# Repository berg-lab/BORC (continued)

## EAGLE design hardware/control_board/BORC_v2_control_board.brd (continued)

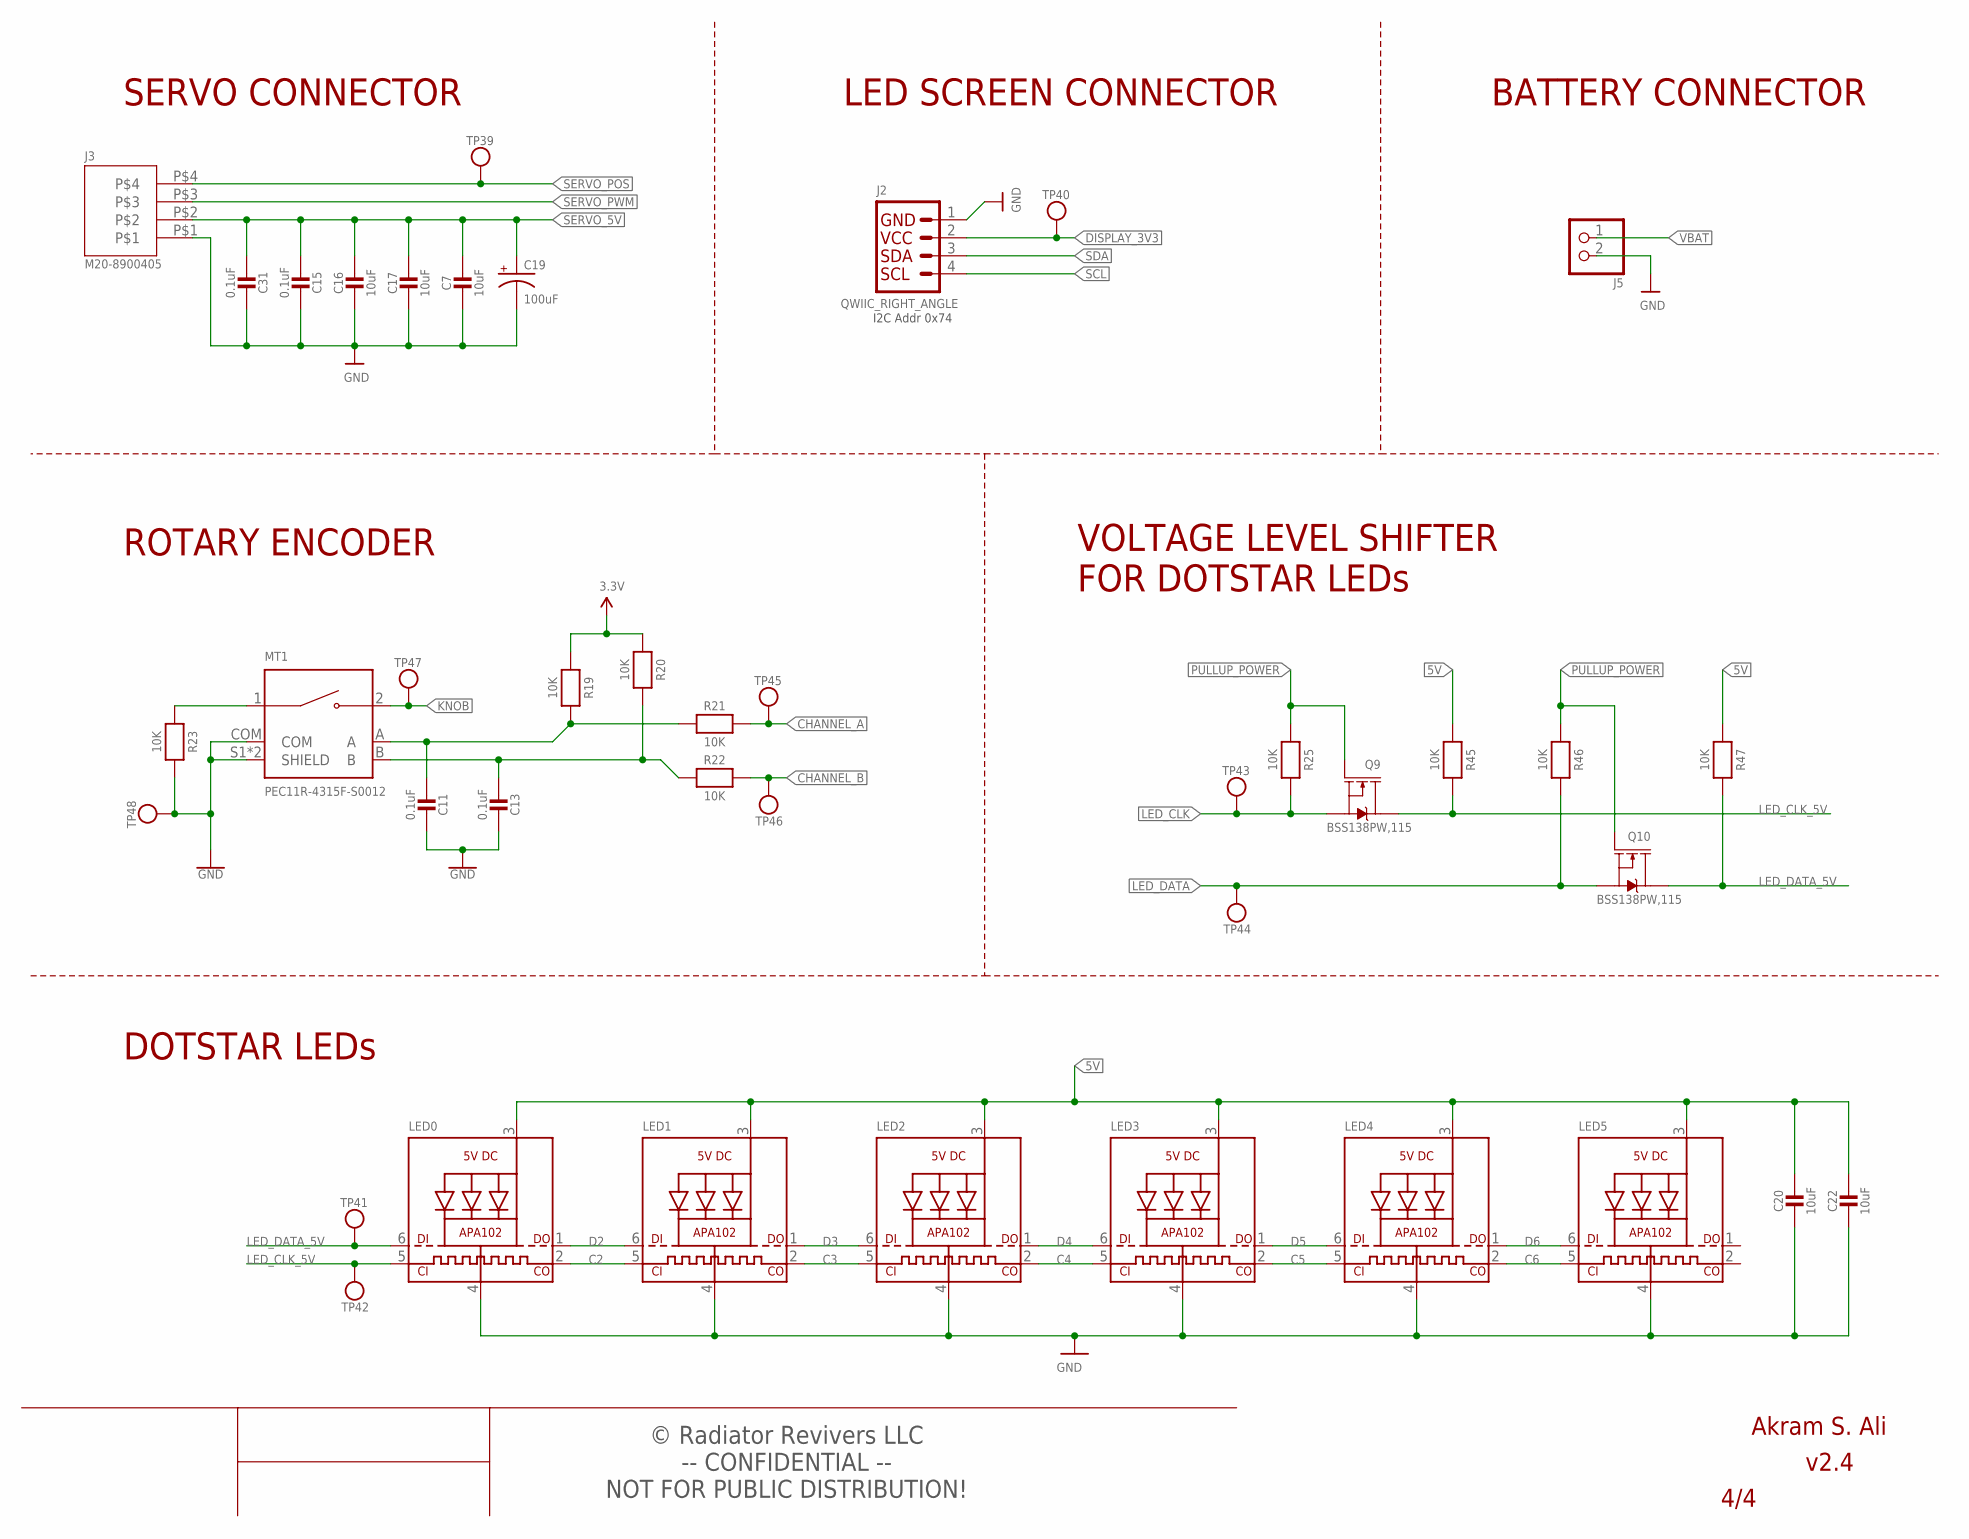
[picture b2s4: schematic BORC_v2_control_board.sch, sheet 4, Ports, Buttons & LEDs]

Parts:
C7, C16, C17, C20, C22: 10uF; MICROBUILDER__0402MP; MPN GRM155R61A106ME11D
C11, C13, C15, C31: 0.1uF; MICROBUILDER__0402MP; MPN GRM155R71H104KE14D
C19: 100uF; PANASONIC_D; MPN A768EB107M1ELAS036
J2: QWIIC_RIGHT_ANGLE; JST04_1MM_RA; MPN SM04B-SRSS-TB(LF)(SN)
J3: M20-8900405; MPN M20-8900405
J5: JST_2PIN-THM-RA; JST-PH-2-THM-RA; MPN S2B-PH-K-S
LED0, LED1, LED2, LED3, LED4, LED5: APA102; APA102_2020; MPN APA102-2020
MT1: PEC11R-4315F-S0012; XDCR_PEC11R-4215F-S0024; MPN PEC11R-4315F-S0012
Q9, Q10: BSS138PW,115; SOT323; MPN BSS138PW,115
R19, R20, R21, R22, R23, R25, R45, R46, R47: 10K; MICROBUILDER__0402MP; MPN RC0402FR-7W10KL
TP39, TP40, TP41, TP42, TP43, TP44, TP45, TP46, TP47, TP48: RX; MICROBUILDER_TESTPOINT_ROUND_1MM

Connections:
5V: C20.1, C22.1, LED0.3 (VDD), LED1.3 (VDD), LED2.3 (VDD), LED3.3 (VDD), LED4.3 (VDD), LED5.3 (VDD), R45.1, R47.1; also elsewhere on the board
A: C11.2, MT1.A, R19.2, R21.1
B: C13.2, MT1.B, R20.2, R22.1
C2: LED0.2 (CKO), LED1.5 (CKI)
C3: LED1.2 (CKO), LED2.5 (CKI)
C4: LED2.2 (CKO), LED3.5 (CKI)
C5: LED3.2 (CKO), LED4.5 (CKI)
C6: LED4.2 (CKO), LED5.5 (CKI)
CHANNEL_A: R21.2, TP45.P$1; also elsewhere on the board
CHANNEL_B: R22.2, TP46.P$1; also elsewhere on the board
D2: LED0.1 (DO), LED1.6 (DI)
D3: LED1.1 (DO), LED2.6 (DI)
D4: LED2.1 (DO), LED3.6 (DI)
D5: LED3.1 (DO), LED4.6 (DI)
D6: LED4.1 (DO), LED5.6 (DI)
DISPLAY_3V3: J2.2, TP40.P$1; also elsewhere on the board
GND: C7.2, C11.1, C13.1, C15.1, C16.2, C17.2, C19.-, C20.2, C22.2, C31.1, J2.1, J3.P$1, J5.2 (1), LED0.4 (GND), LED1.4 (GND), LED2.4 (GND), LED3.4 (GND), LED4.4 (GND), LED5.4 (GND), MT1.COM, MT1.S1 (SHIELD), MT1.S2 (SHIELD), R23.2, TP48.P$1; also elsewhere on the board
KNOB: MT1.2, TP47.P$1; also elsewhere on the board
LED_CLK: Q9.2 (S), R25.2, TP43.P$1; also elsewhere on the board
LED_CLK_5V: LED0.5 (CKI), Q9.3 (D), R45.2, TP42.P$1
LED_DATA: Q10.2 (S), R46.2, TP44.P$1; also elsewhere on the board
LED_DATA_5V: LED0.6 (DI), Q10.3 (D), R47.2, TP41.P$1
unnamed: MT1.1, R23.1
PULLUP_POWER: Q9.1 (G), Q10.1 (G), R25.1, R46.1; also elsewhere on the board
SCL: J2.4; also elsewhere on the board
SDA: J2.3; also elsewhere on the board
SERVO_5V: C7.1, C15.2, C16.1, C17.1, C19.+, C31.2, J3.P$2; also elsewhere on the board
SERVO_POS: J3.P$4, TP39.P$1; also elsewhere on the board
SERVO_PWM: J3.P$3; also elsewhere on the board
VBAT: J5.1 (2); also elsewhere on the board
VCC: R19.1, R20.1; also elsewhere on the board

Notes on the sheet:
ROTARY ENCODER
SERVO CONNECTOR
BATTERY CONNECTOR
LED SCREEN CONNECTOR
DOTSTAR LEDs
VOLTAGE LEVEL SHIFTER FOR DOTSTAR LEDs
I2C Addr 0x74
-- CONFIDENTIAL -- NOT FOR PUBLIC DISTRIBUTION!
© Radiator Revivers LLC

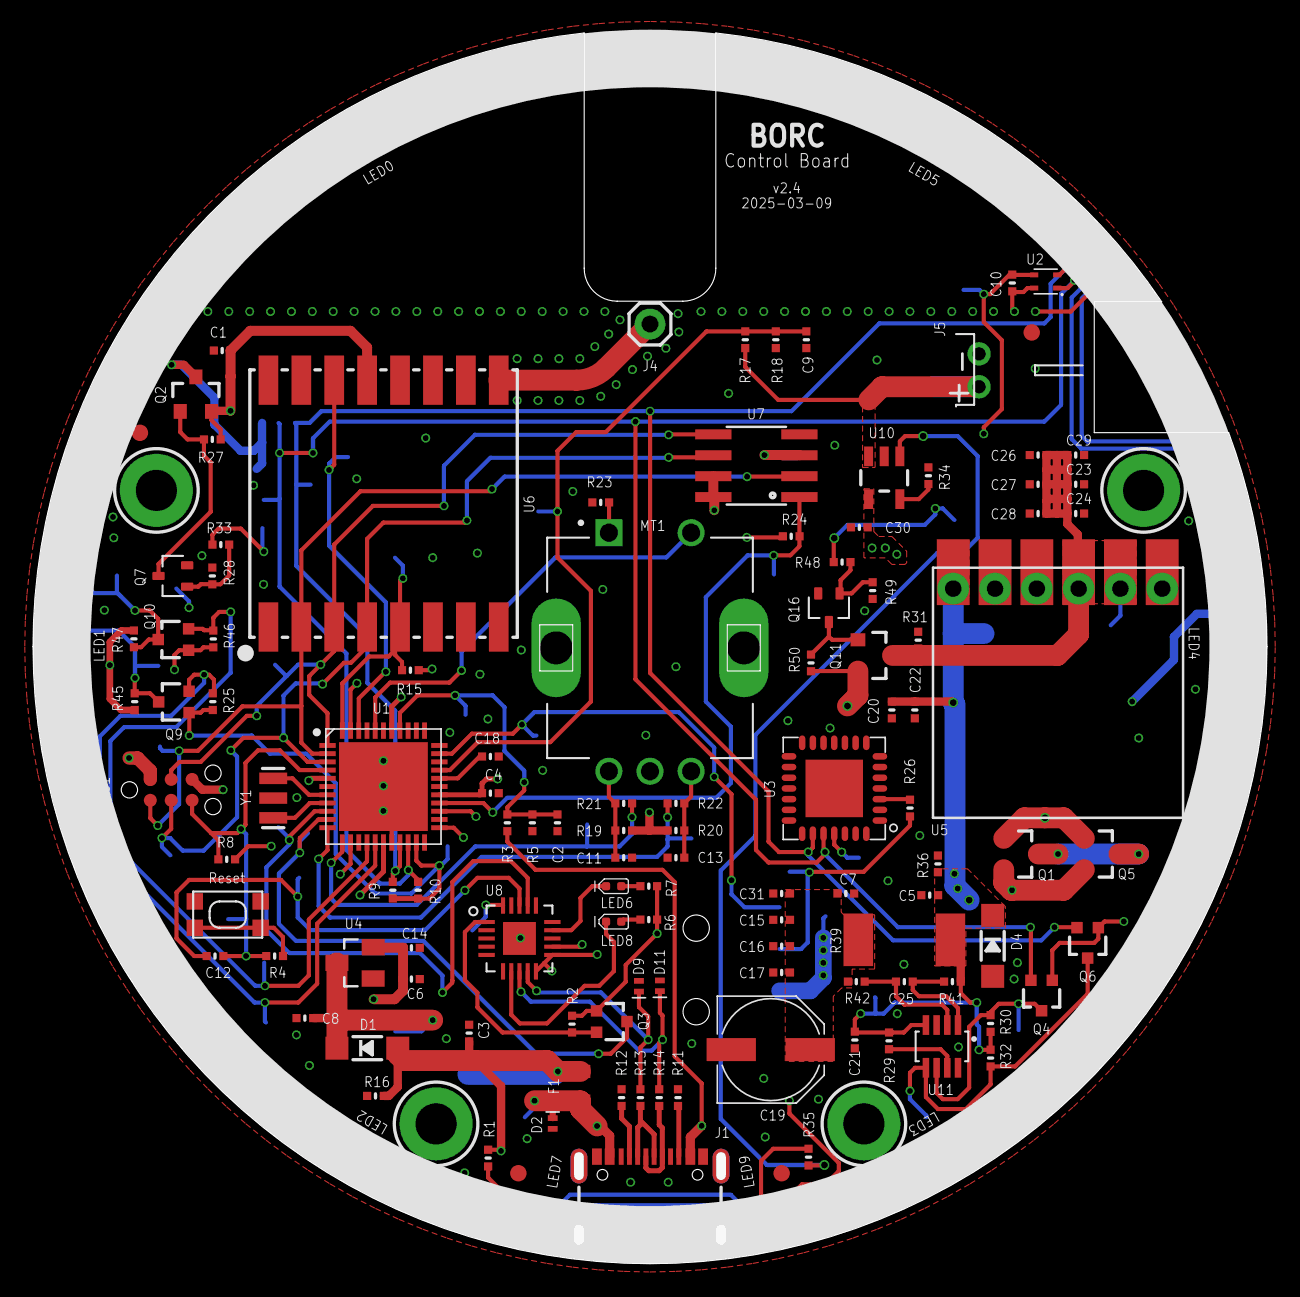
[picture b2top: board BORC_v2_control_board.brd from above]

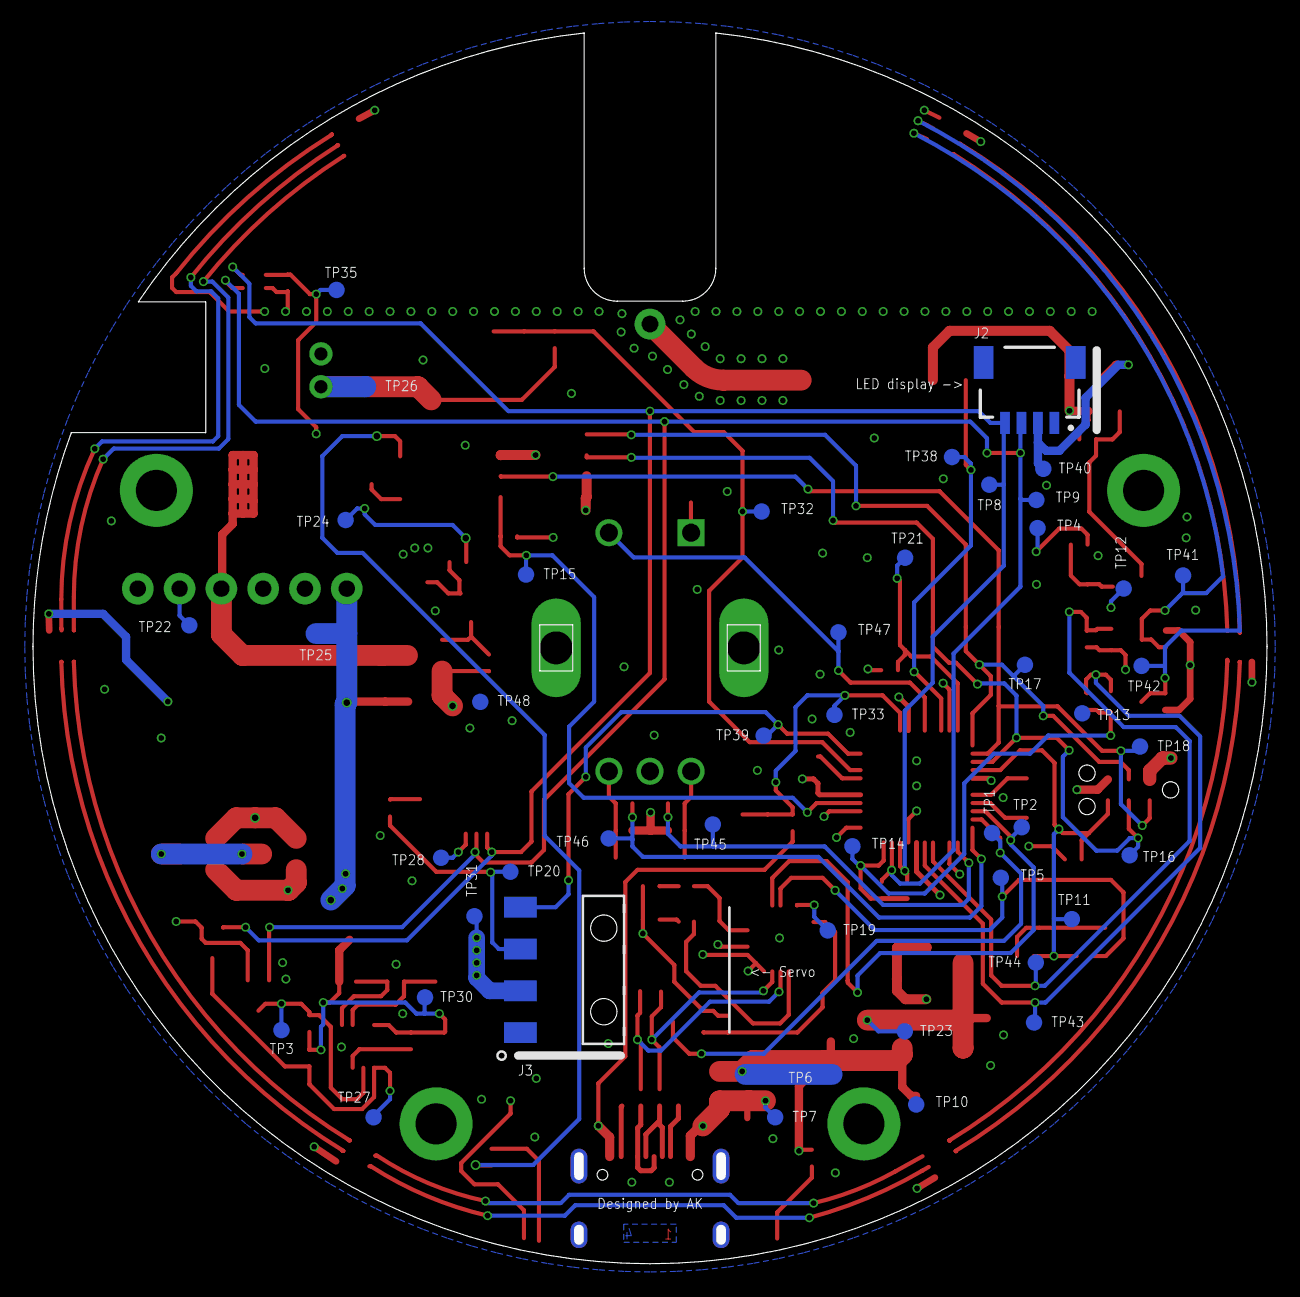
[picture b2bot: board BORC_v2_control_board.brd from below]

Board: 4 copper layers, 74.4 x 74.2 mm, 174 parts (46 on the bottom side), 82 nets.

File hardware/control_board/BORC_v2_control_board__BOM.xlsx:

Parts | Qty | Value | Manufacturer | MPN | Description
J4 | 1 |  |  | HP-915-2.5A-9T | 915 MHz right angled helical spring antenna, 17.5 mm/0.68", 2.15 dBi gain, 50Ω 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
J5 | 1 | 2 POS 2.0mm | JST Sales America Inc. | S2B-PH-K-S | Connector Header Through Hole, Right Angle 2 position 0.079" (2.00mm)
R39 | 1 | 0.1/1%/2W | Vishay Dale | RCWE2512R100FKEA | 100 mOhms ±1% 2W Chip Resistor 2512 (6432 Metric) Automotive AEC-Q200, Current 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
C2, C3, C4, C5, C6, C9, C10, C11, C12, C13, C15, C18, C21, C25, C31 | 15 | 0.1uF | Murata Electronics | GRM155R71H104KE14D | 0.1 µF ±10% 50V Ceramic Capacitor X7R 0402 (1005 Metric)
R41, R42 | 2 | 10 | YAGEO | RC0402FR-0710RL | 10 Ohms ±1% 0.063W, 1/16W Chip Resistor 0402 (1005 Metric) Moisture Resistant T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
C19 | 1 | 100uF | KEMET | A768EB107M1ELAS036 | 100 µF 25 V Aluminum - Polymer Capacitors Radial, Can - SMD 36mOhm 2000 Hrs @ 1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
R2, R8, R15, R19, R20, R21, R22, R23, R24, R25, R27, R28, R29, R30, R31, R32, R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 | 23 | 10K | YAGEO | RC0402FR-7W10KL | 10 kOhms ±1% 0.125W, 1/8W Chip Resistor 0402 (1005 Metric) Moisture Resistant T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
R3, R5, R17, R18 | 4 | 10M | YAGEO | RC0402FR-0710ML | 10 MOhms ±1% 0.063W, 1/16W Chip Resistor 0402 (1005 Metric) Moisture Resistant 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
C1, C7, C8, C14, C16, C17, C20, C22, C23, C24, C26, C27, C28, C29, C30 | 15 | 10uF | Murata Electronics | GRM155R61A106ME11D | 10 µF ±20% 10V Ceramic Capacitor X5R 0402 (1005 Metric)
Y1 | 1 | 16 MHz | Murata Electronics | CSTNE16M0V530000R0 | 16 MHz Ceramic Resonator Built in Capacitor 15 pF ±0.3% 40 Ohms -40°C ~ 85°C Su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
R1, R6, R7, R33, R34, R48 | 6 | 1K | YAGEO | RC0402FR-071KL | 1 kOhms ±1% 0.063W, 1/16W Chip Resistor 0402 (1005 Metric) Moisture Resistant T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
R4, R26 | 2 | 220 | YAGEO | RC0402FR-13220RL | 220 Ohms ±1% 0.063W, 1/16W Chip Resistor 0402 (1005 Metric) Moisture Resistant 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
R13, R14 | 2 | 27 | YAGEO | RC0402FR-0727RL | 27 Ohms ±1% 0.063W, 1/16W Chip Resistor 0402 (1005 Metric) Moisture Resistant T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
R9, R10, R16 | 3 | 4.7K | YAGEO | RC0402FR-074K7L | 4.7 kOhms ±1% 0.063W, 1/16W Chip Resistor 0402 (1005 Metric) Moisture Resistant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
R11, R12 | 2 | 5.1K | YAGEO | RC0402FR-135K1L | 5.1 kOhms ±1% 0.063W, 1/16W Chip Resistor 0402 (1005 Metric) Thick Film
U6 | 1 | 915MHz | HOPERF | RFM69HCW | HOPERF RFM69H ISM Transceiver Module General ISM 915MHz Surface Mount
LED0, LED1, LED2, LED3, LED4, LED5 | 6 | APA102-2020 | Shenzhen LED Color Opto Electronic CO.,LTD | APA102-2020 | APA102-2020 Super LED/DotStar Pixels
U7 | 1 | W25X40CLSNIG | Winbond Electronics | W25X40CLSNIG | FLASH Memory IC 4Mbit SPI 104 MHz 8-SOIC
U1 | 1 | ATMEGA1284P-MU | Microchip Technology | ATMEGA1284P-MU | AVR AVR® ATmega Microcontroller IC 8-Bit 20MHz 128KB (64K x 16) FLASH 44-VQFN (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
Q3, Q4, Q6, Q9, Q10 | 5 | BSS138PW,115 | Nexperia USA Inc. | BSS138PW,115 | N-Channel 60 V 320mA (Ta) 260mW (Ta), 830mW (Tc) Surface Mount SOT-323
U8 | 1 | FT231XQ-R | FTDI, Future Technology Devices International Ltd | FT231XQ-R | USB Bridge, USB to UART USB 2.0 UART Interface 20-QFN (4x4)
LED8 | 1 | GREEN | Inolux | IN-S42ATG | Green 525nm LED Indication - Discrete 3.3V 0402 (1005 Metric)
U11 | 1 | INA219AIDCNR | Texas Instruments | INA219AIDCNR | Current Monitor Regulator High-Side 10mA SOT-23-8
J3 | 1 | M20-8900405 | Harwin Inc. | M20-8900405 | Connector Header Surface Mount, Right Angle 4 position 0.100" (2.54mm)
U4 | 1 | 3.3V, 250mA | Microchip Technology | MCP1703T-3302E/CB | Linear Voltage Regulator IC Positive Fixed 1 Output 250mA SOT-23A-3
U10 | 1 | MCP73831T-2ACI/OT | Microchip Technology | MCP73831T-2ACI/OT | Charger IC Lithium Ion/Polymer SOT-23-5
F1 | 1 | 6V 2.6A | Bourns Inc. | MF-PSML260/6-2 | Polymeric PTC Resettable Fuse 6V 2.6 A Ih Surface Mount 0805 (2012 Metric), Con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
U3 | 1 | PCA9685 | NXP USA Inc. | PCA9685BS,118 | LED Driver IC 16 Output Linear PWM Dimming 25mA 28-HVQFN (6x6)
MT1 | 1 | PEC11R-4315F-S0012 |  | PEC11R-4315F-S0012 | Rotary Encoder Mechanical 12 Quadrature (Incremental) Vertical
U5 | 1 | 4012 | Pololu Corporation | U3V40F5 | Non-Isolated PoL Module DC DC Converter 1 Output 5V 3.5A 1.3V - 5V Input
J2 | 1 | 4 POS 1mm | JST Sales America Inc. | SM04B-SRSS-TB(LF)(SN) | Connector Header Surface Mount, Right Angle 4 position 0.039" (1.00mm)
LED6, LED7 | 2 | RED | Inolux | IN-S42ATR | Red 631nm LED Indication - Discrete 2.1V 0402 (1005 Metric)
U2 | 1 | SHT40-BD1B | Sensirion AG | SHT40-BD1B-R3 | Humidity, Temperature 0 ~ 100% RH I²C ±1.8% RH 6 s Surface Mount
D2, D9, D11 | 3 | SP0402U-ULC-01ETG | Littelfuse Inc. | SP0402U-ULC-01ETG | 9.2V (Typ) Clamp 2A (8/20µs) Ipp Tvs Diode Surface Mount 0402/2DFN (1x0.60)
SW1 | 1 | SPST_TACT-KMR2 | C&K | KMR221GLFS | Tactile Switch SPST-NO Top Actuated Surface Mount
D1, D4 | 2 | SS34LWH | Taiwan Semiconductor Corporation | SS34LWH | Diode 40 V 3A Surface Mount SOD-123W
Q1, Q2, Q5, Q11 | 4 | SSM3J338R,LF | Toshiba Semiconductor and Storage | SSM3J338R,LF | P-Channel 12 V 6A (Ta) 1W (Ta) Surface Mount SOT-23F
Q7, Q16 | 2 | UMT3904T106 | Rohm Semiconductor | UMT3904T106 | Bipolar (BJT) Transistor NPN 40 V 200 mA 300MHz 200 mW Surface Mount UMT3
J1 | 1 | CONN RCP USB2.0 TYP C 24P SMD RA | GCT | USB4105-GF-A | USB-C (USB TYPE-C) USB 2.0 Receptacle Connector 24 (16+8 Dummy) Position Surfac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
LED9 | 1 | YELLOW | Inolux | IN-S42ATY | Yellow 592nm LED Indication - Discrete 1.9V 0402 (1005 Metric)

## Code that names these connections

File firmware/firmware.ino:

#include "globals.h"
#include "common.h"
#include <avr/wdt.h>
#include "i2c.h"


//=========================================================================================================
// Setup
//=========================================================================================================
void setup()
{    
    Serial.begin(115200);
    Serial.println("begin");

    // Use a system-wide I2C bus speed of 400 Khz
    twi_setFrequency(400000);

    // blink aqua for 1 second to show device booted
    Led.init();
    Led.set(AQUA, 1000, true);

    // << WE WANT THIS TO BE AVAILABLE WHEN THE OTHER .init() ROUTINES ARE CALLED >>>
    EEPROM.read();

    // <<< WE WANT THIS TO BE AVAILABLE WHEN System.init() IS CALLED >>>
    Logger.init();

    // << WE WANT THIS TO BE AVAILABLE WHEN THE OTHER .init() ROUTINES ARE CALLED >>>
    System.init();
    
    // Fetch the current temperature
    SHT31.read_f(&System.temp_f);

    // initialize the power manager
    PowerMgr.init();

    // turn power all for all devices
    PowerMgr.powerOnAll(); 

    // initialize all devices
    INA219.init(CURRENT_SENSE_ADDRESS);
    Knob.init(CHANNEL_A, CHANNEL_B, CLICK_PIN);
    Display.init(LED_MATRIX_ADDRESS);
    Servo.init();
    Radio.init();

    // Initilize the Temperature controller
    TempCtrl.init();

    // restore the system orientation from EEPROM
    System.set_orientation(ee.orientation);

    // set system mode to the actual run mode
    System.return_to_run_mode();
  
    // if the servo hasn't been successfully calibrated, do so
    // if (ee.is_servo_calibrated == NOTCAL)  Servo.calibrate_bare();

    // Transmit a packet of telemetry on bootup
    Radio.transmit_telemetry();
    Radio.transmit_config(3);

    //-------------------------------------------------------
    //              FROM HERE DOWN IS DEBUG CODE
    //-------------------------------------------------------
    // read temp and hum from sensor
    float temp_f, rh;
    if (SHT31.read_f(&temp_f, &rh))
    {
      aprintf("Temperature: %1.2f, RH: %1.2f\n", temp_f, rh);
    }

    // Servo.move_to_pwm(92, 4000, true);
    // Servo.move_to_pwm(542, 4000, true);  
    //-------------------------------------------------------

}
//=========================================================================================================

//=========================================================================================================
// BIG LOOP
//=========================================================================================================
void loop()
{
    wdt_reset(); //pat the dog...

    USB.execute();

    SerialServer.execute();

    SleepMgr.execute();

    Led.execute();
  
    switch (System.iface_mode)
    {
      case MANUAL_MODE   : ManualModeMgr.execute();    break;
      case MENU_MODE     : MenuMgr.execute();          break;
      case SETPOINT_MODE : SetpointModeMgr.execute();  break;
    }
}
//=========================================================================================================

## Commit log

2022-09-29 clean up for release
2023-09-04 added bare servo calibration command in serial server
2024-02-02 Merged control board and power board, updated LED board
2024-02-04 v2.1 - bug fixes and design update
2024-02-04 v2.1 - bug fixes and design update
    removed power board files
2025-01-14 v2.3 - Control board update
    - Added two P-channel MOSFETs in parallel for reverse protection of the battery to reduce RDS(ON)
    - Reduce MOSFETs gate pull-down resistor from 10k to 4.7k (account for increase in gate capacitance when using 2 FETs instead of 1)
    - Replace P-channel MOSFETS with SSM3J338R,LF - higher Id (6A) and lower RDS(ON) (17mohm)
    - INA219 is now powered from the 5V bus instead of 3.3V bus. This is to avoid potential issues in performance if 3.3V bus voltage drops down under 2.7V when servo is moving. All other sensors and ICs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
    - Added logic level shifters for INA219 I2C bus to translate from 5V to 3.3V
    - Replaced the 3.3V power on all voltage
2025-01-15 Added PNP file for v2.3 control board
2025-01-15 Added PNP file for v2.1 LED board
2025-03-09 v2.4 - Control board bug fixes
    - Remove extra 10K pull-ups on 3.3V I2C level shifter, since 4.7K I2C pull-ups already exist on the bus
    - Remove pull-up power circuitry. Now toggling directly from GPIO
    - Add NPN transistor to gate of Q2 to toggle display power properly
    - Add 10k bleed resistors to input and output of 5V boost regulator to drain the capacitors when power is turned off
    - Add layer numbers on each layer for reference
    - Made antenna trace curved
2025-08-18 Added PnP and BOM files
2025-08-18 Added BOM and PnP files
